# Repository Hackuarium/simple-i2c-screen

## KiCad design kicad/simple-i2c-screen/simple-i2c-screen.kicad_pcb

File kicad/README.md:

## incubator
This design has the following components:

- Power supply plug: 5V to 28 V
- Top-bottom 5 pin 2.54 mm connector.
- 5 V buck converter
- ATMEGA328P mmicrocontroller
- ISP connector
- LCD 16x2 display
- RJ12 connector for I2C communication

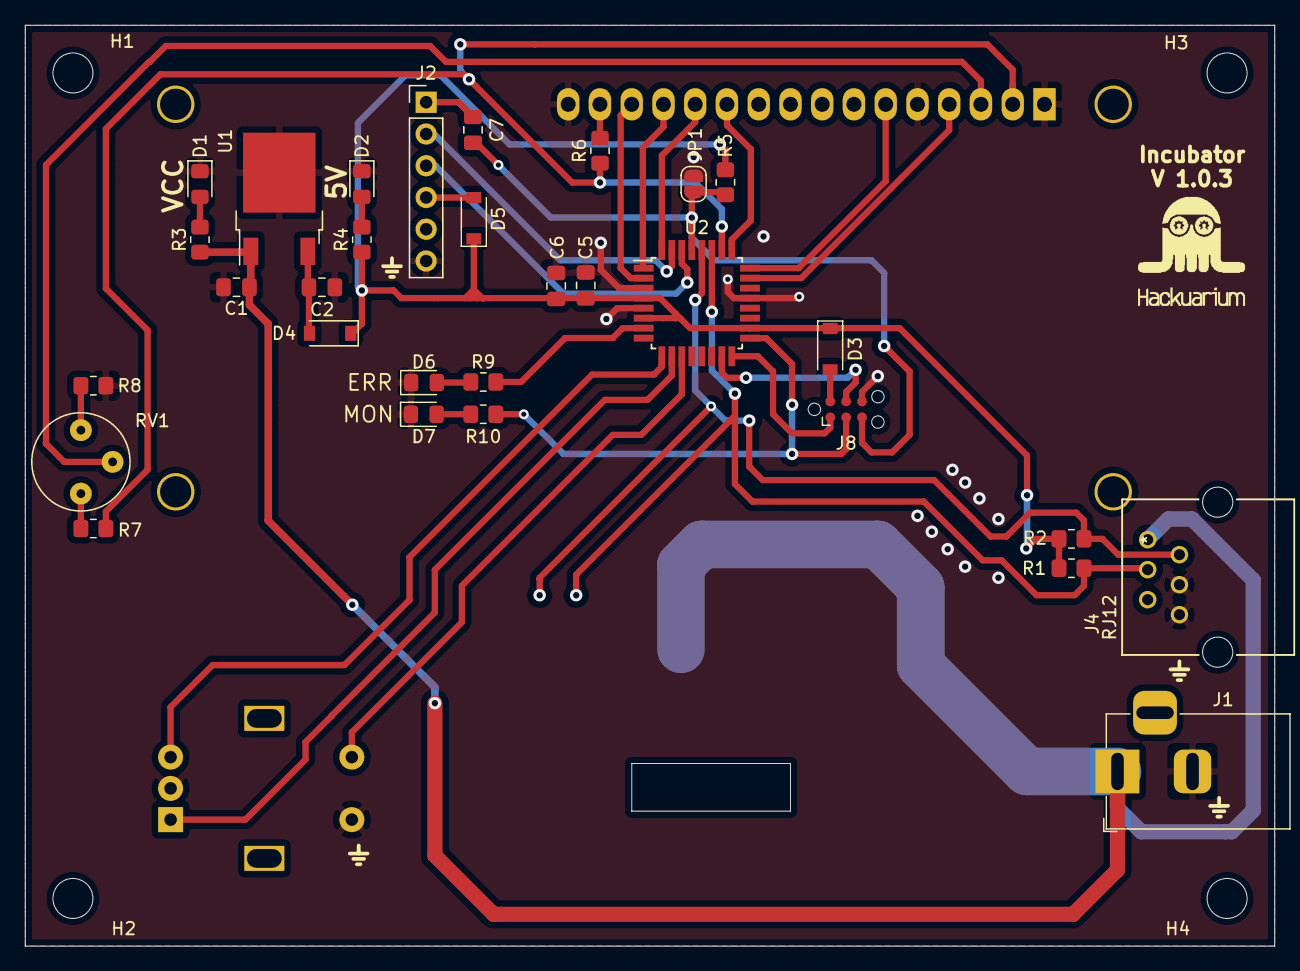
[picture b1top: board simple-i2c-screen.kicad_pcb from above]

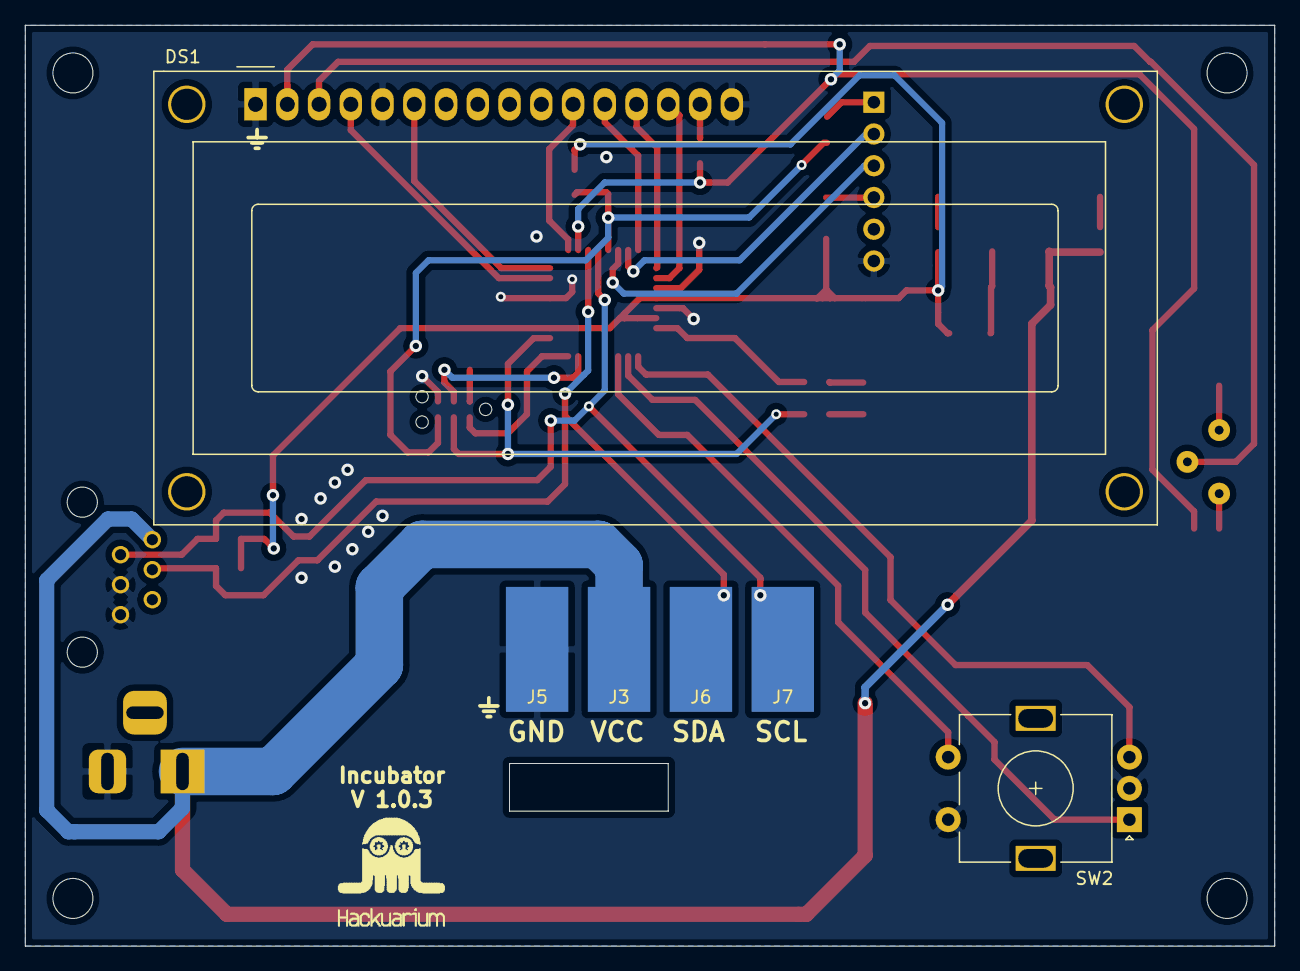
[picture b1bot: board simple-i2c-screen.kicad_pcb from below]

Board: 2 copper layers, 99.9 x 73.7 mm, 42 parts (7 on the bottom side), 34 nets.

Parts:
C1: 0.33u; C_0805_2012Metric_Pad1.18x1.45mm_HandSolder
C2, C6, C7: 100n; C_0805_2012Metric_Pad1.18x1.45mm_HandSolder
C5: 10u; C_0805_2012Metric_Pad1.18x1.45mm_HandSolder
D1, D2: RED; LED_0805_2012Metric_Pad1.15x1.40mm_HandSolder
D3, D4, D5: MBR0520LT; D_SOD-123
D6, D7: GREEN; LED_0805_2012Metric_Pad1.15x1.40mm_HandSolder
DS1: WC1602A
H1, H2, H3, H4: MountingHole; MountingHole_3.2mm_M3
J1: Barrel_Jack_MountingPin; BarrelJack_Horizontal
J2: Conn_01x06; PinHeader_1x06_P2.54mm_Vertical
J3, J5, J6, J7: Conn_01x01; SolderWirePad_1x01_SMD_5x10mm
J4: RJ12; E5566-Q0LK22-L
J8: Conn_02x03_Odd_Even; Tag-Connect_TC2030-IDC-NL_2x03_P1.27mm_Vertical
JP1: SolderJumper_2_Open; SolderJumper-2_P1.3mm_Open_RoundedPad1.0x1.5mm
R1, R2, R3: 10k; R_0805_2012Metric_Pad1.20x1.40mm_HandSolder
R4, R9, R10: 1k; R_0805_2012Metric_Pad1.20x1.40mm_HandSolder
R5: 100k; R_0805_2012Metric_Pad1.20x1.40mm_HandSolder
R6: 0; R_0805_2012Metric_Pad1.20x1.40mm_HandSolder
R7, R8: 100; R_0805_2012Metric_Pad1.20x1.40mm_HandSolder
RV1: 10k; Potentiometer_Bourns_3339P_Vertical_HandSoldering
SW2: Rotary_Encoder_Switch; RotaryEncoder_Alps_EC11E-Switch_Vertical_H20mm
U1: LM78M05_TO252; TO-252-2
U2: ATmega328P-AU; TQFP-32_7x7mm_P0.8mm
logoHackuarium: logoHackuarium
logoHackuarium#2: logoHackuarium

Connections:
12V: C1.1, J1.1, J3.1, J4.1, R3.1, U1.1
C0: DS1.4, U2.23
C1: DS1.6, U2.24
C2: DS1.11, U2.25
C3: DS1.2, R6.1, R7.1, U2.26
D2: DS1.12, U2.32
D3: DS1.13, U2.1
D4: DS1.14, U2.2
D5: SW2.B, U2.9
D6: SW2.A, U2.10
D7: SW2.S1, U2.11
ERROR: R9.1, U2.7
GND: C1.2, C2.2, C5.2, C6.2, D1.1, D2.1, D6.1, D7.1, DS1.1, DS1.5, DS1.16, J1.2, J2.6, J4.4, J4.6, J5.1, J8.6, JP1.1, R8.2, SW2.C, SW2.S2, U1.2, U2.3, U2.5, U2.21
MISO: J8.1, U2.16
MOSI: J8.4, U2.15
unnamed: C2.1, D4.2, U1.3
unnamed: C7.2, J2.1
unnamed: D1.2, R3.2
unnamed: D2.2, R4.2
unnamed: D3.2, J8.2
unnamed: D5.2, J2.4
unnamed: D6.2, R9.2
unnamed: D7.2, R10.2
unnamed: DS1.3, RV1.2
unnamed: DS1.15, R6.2
unnamed: R7.2, RV1.3
unnamed: R8.1, RV1.1
RX: J2.3, U2.30
SCK|MONITORING: J8.3, R10.1, U2.17
SCL: J4.2, J7.1, R2.2, U2.28
SDA: J4.3, J6.1, R1.2, U2.27
TX: J2.2, U2.31
VIN: C5.1, C6.1, D3.1, D4.1, D5.1, R1.1, R2.1, R4.1, R5.1, U2.4, U2.6, U2.18
~RESET: C7.1, J8.5, JP1.2, R5.2, U2.29

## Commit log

2021-08-05 docs: Kicad/README.m created
2021-08-23 refactor: Kicad design updated
2021-08-23 feat: Platformio code
2021-08-23 feat: ibom generated
2021-08-23 fix: ibom preview
2021-08-24 fix: change top-bottom connector for individual pad
2021-09-14 fix: fan size and push button position
2021-09-14 fix: fan size and push button position and news routes
2021-09-15 fix: fan connection
2021-09-15 refactor:Step-down IC was changed
2021-09-16 style: change some positions
2021-09-21 refactor: final test version
2021-11-05 feat: LCD
2021-11-08 feat: THD files
2021-11-08 fix: PCINT pins enables and LCD Thread created
2021-11-08 refactor: PlatformIO project
2021-11-08 fix: iss #1: add ERROR and BLINKING LED, iss #2: solved
2021-11-16 feat: WireMaster file
2021-11-17 docs: WireMaster communication
2021-11-17 feat: WireMaster communication success!
2021-11-17 fix: same Serial format to print I2C results
2021-11-17 fix: Status 2nd page in screen
2021-11-17 feat: store I2C slave parameters locally
2021-11-18 refactor: rename folders and create simple-i2c-screen project in kicad
2021-11-18 fix: version 1.0.2 of the PCB change size holes M4 -> M3 and changes their position
2021-11-18 refactor: version 1.0.3 for PCB change MOITORING_LED to pin 13 like Arduino
2021-11-18 refactor: clean BioParams.h
2021-11-18 test: I2C read and write parameters from LCD-push button using simple-incubator
2021-11-18 chore: add gitignore
2021-11-18 chore: reduce number of parameters
2021-11-18 chore: activate monitoring, error and logger
2021-11-18 chore: simplify code
2021-11-19 perf: check Threads stack and reduce it
2021-11-19 refactor: new names for Thread files
2022-02-12 refactor: removed BioFunc.* and renamed BioParams -> Funcs.*
2022-02-12 refactor: BioI2C.* -> I2C.*

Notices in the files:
parts and their libraries:
Copyright 2016 Accelerated Designs. All rights reserved.
